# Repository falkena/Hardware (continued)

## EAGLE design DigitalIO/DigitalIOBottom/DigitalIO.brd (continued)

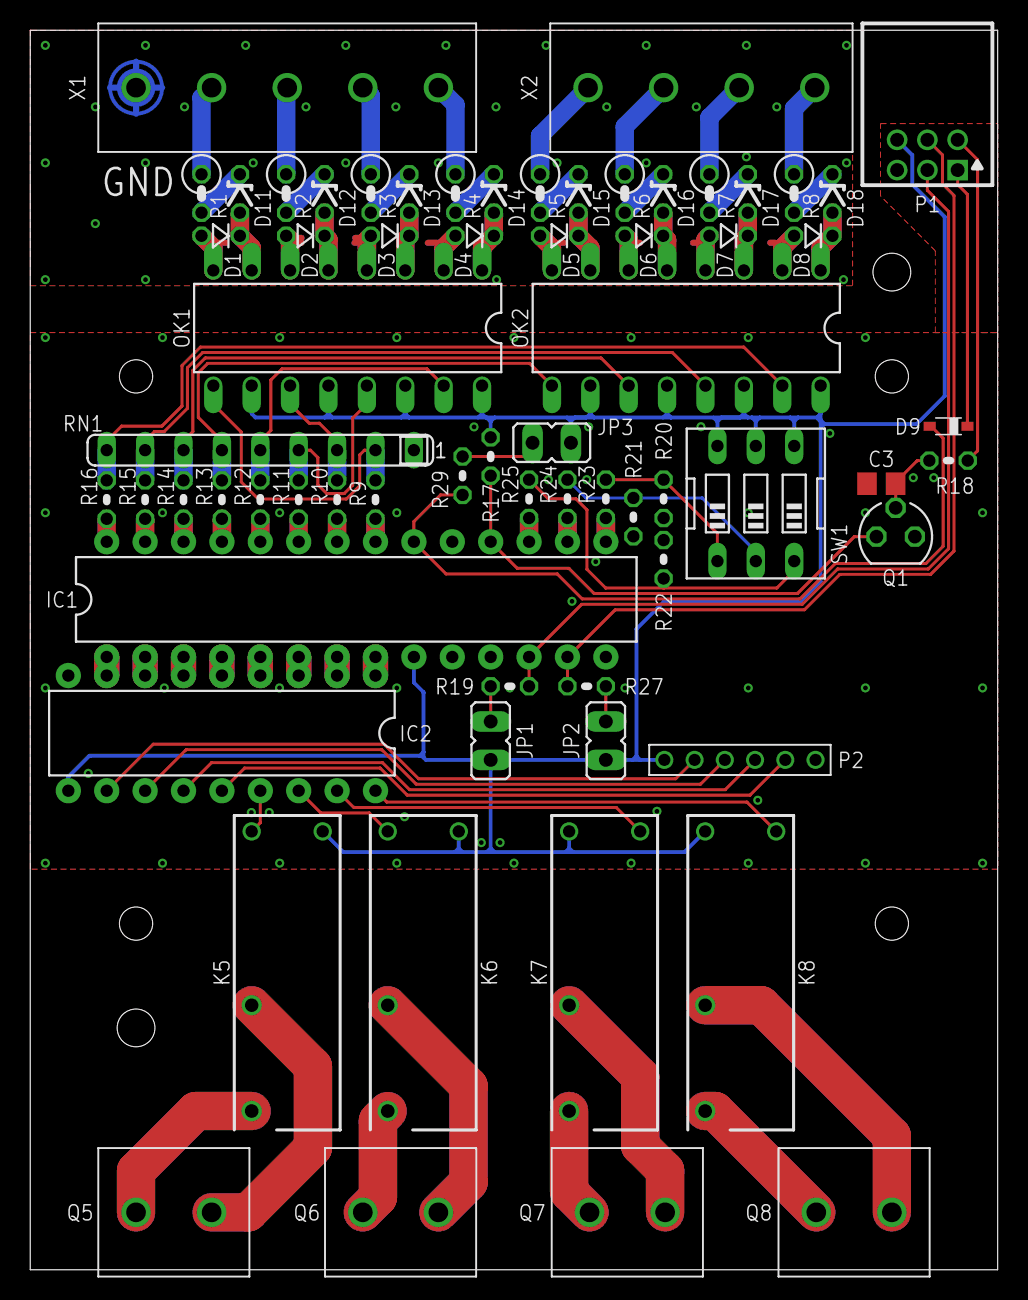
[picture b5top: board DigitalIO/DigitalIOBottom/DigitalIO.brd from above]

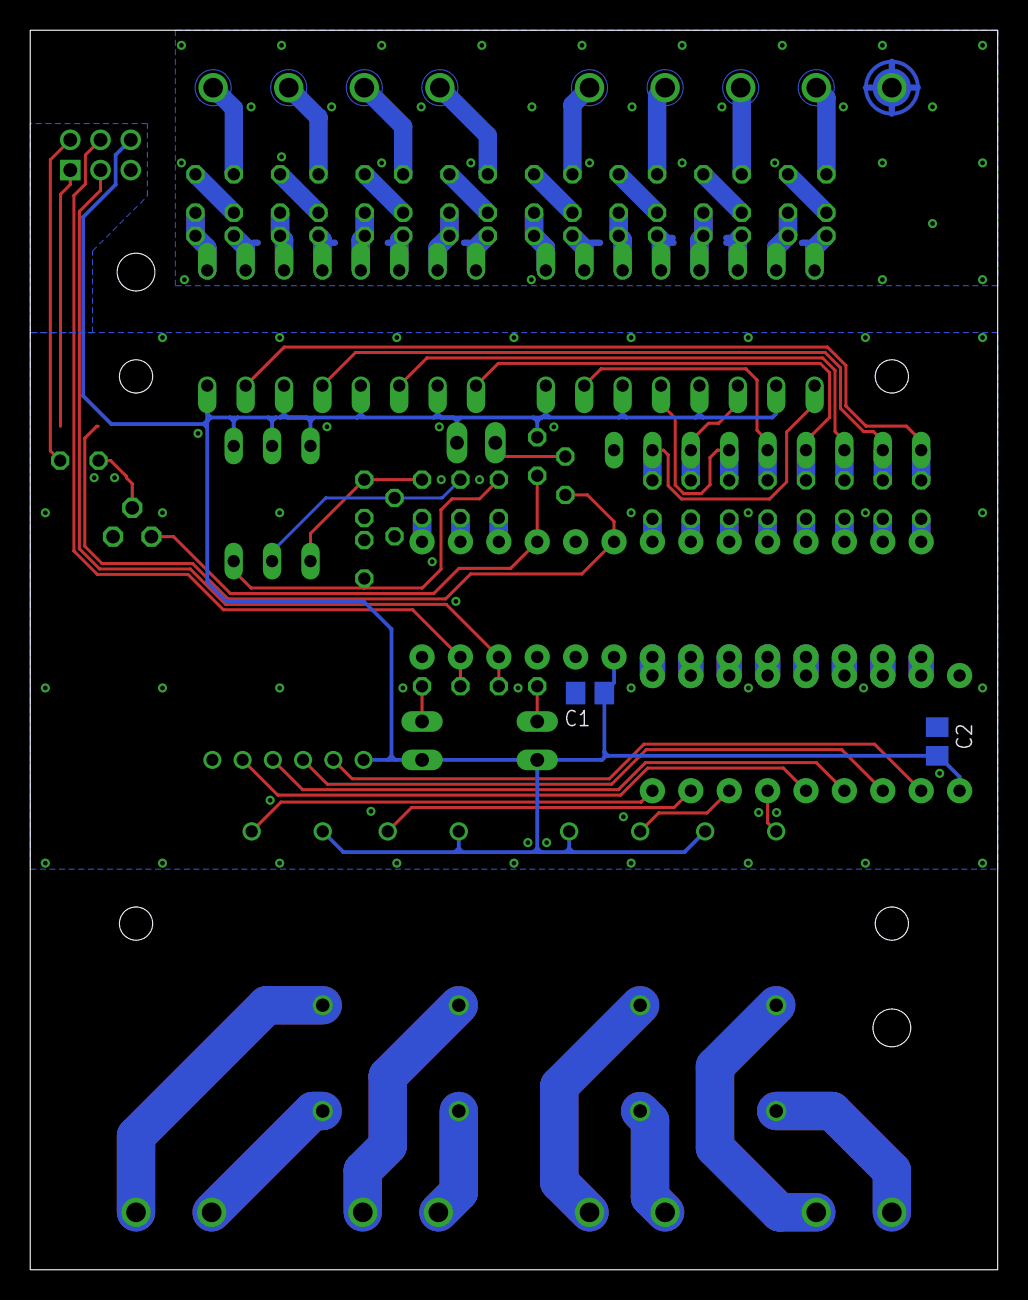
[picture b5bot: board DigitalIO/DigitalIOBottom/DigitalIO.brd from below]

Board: 2 copper layers, 64.0 x 82.0 mm, 69 parts (2 on the bottom side), 83 nets.

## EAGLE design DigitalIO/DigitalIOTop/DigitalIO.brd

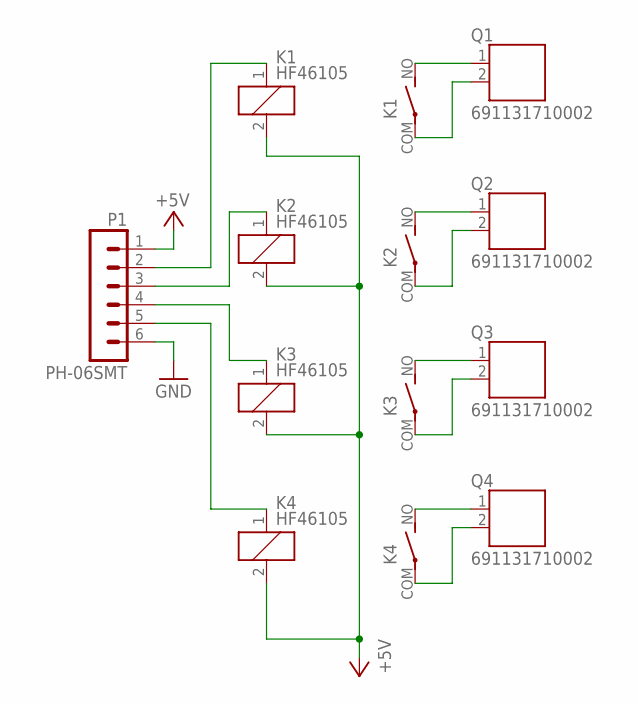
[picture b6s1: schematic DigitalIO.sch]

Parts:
K1, K2, K3, K4: HF46105; HF46
P1: PH-06SMT; S6B-PH-SM4
Q1, Q2, Q3, Q4: 691131710002

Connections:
+5V: K1.2, K2.2, K3.2, K4.2, P1.1
GND: P1.6
unnamed: K2.1, P1.3
unnamed: K4.1, P1.5
unnamed: K1.1, P1.2
unnamed: K1.NO (S), Q1.1
unnamed: K1.COM, Q1.2
unnamed: K2.NO (S), Q2.1
unnamed: K2.COM, Q2.2
unnamed: K3.NO (S), Q3.1
unnamed: K3.COM, Q3.2
unnamed: K4.NO (S), Q4.1
unnamed: K4.COM, Q4.2
unnamed: K3.1, P1.4

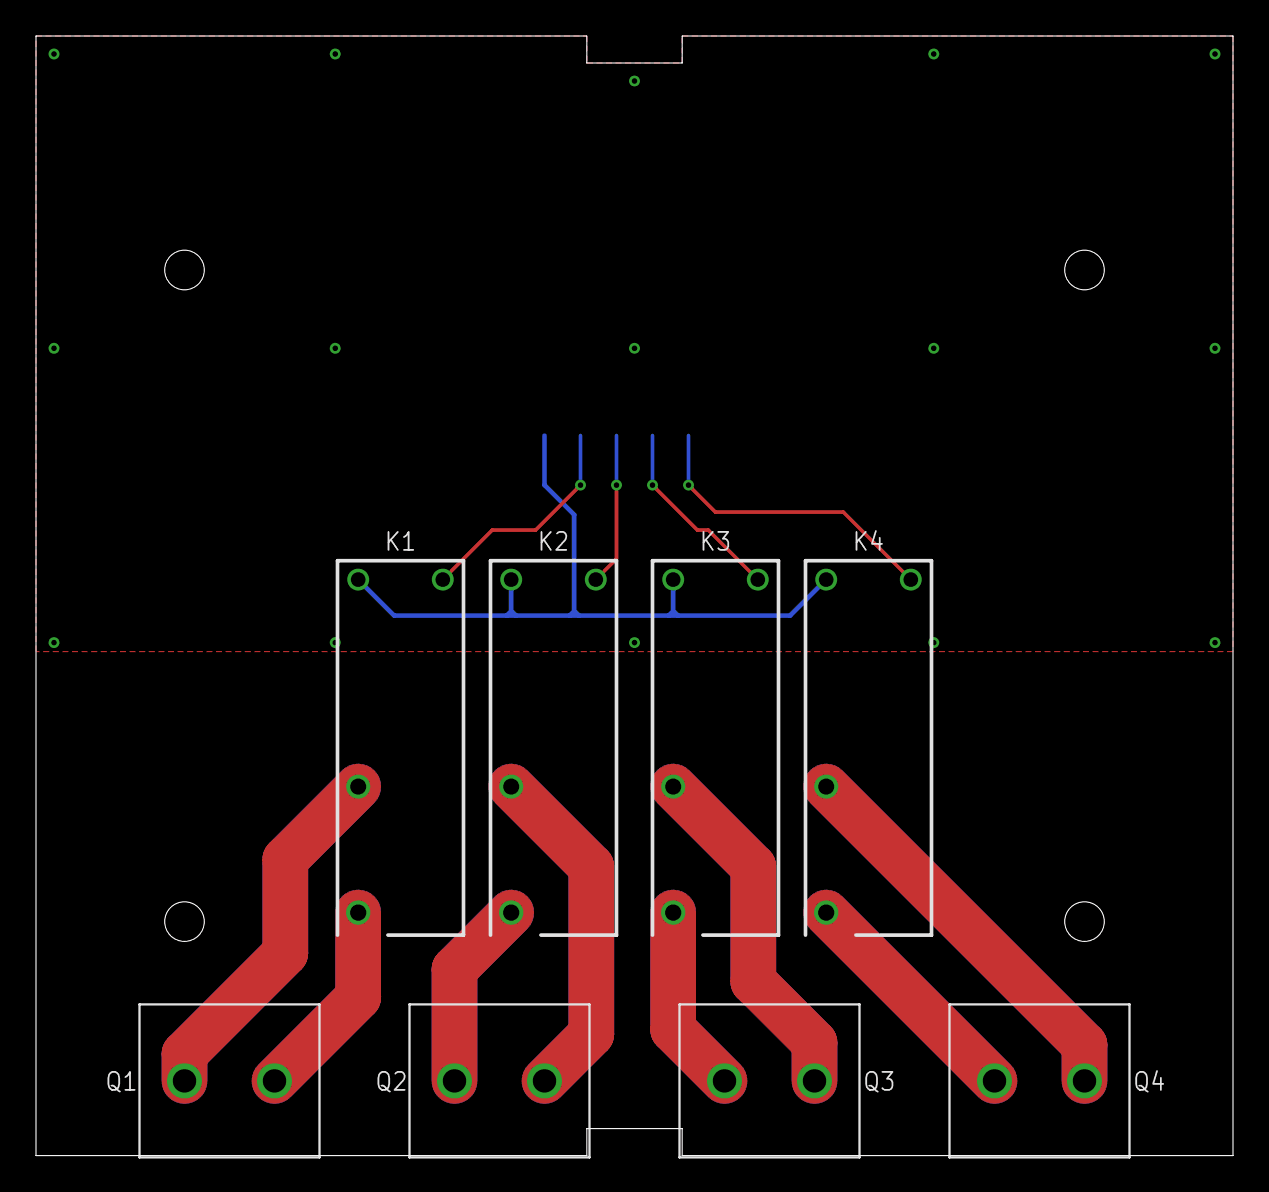
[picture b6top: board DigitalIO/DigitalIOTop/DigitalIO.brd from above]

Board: 2 copper layers, 66.5 x 62.2 mm, 9 parts (1 on the bottom side), 13 nets.

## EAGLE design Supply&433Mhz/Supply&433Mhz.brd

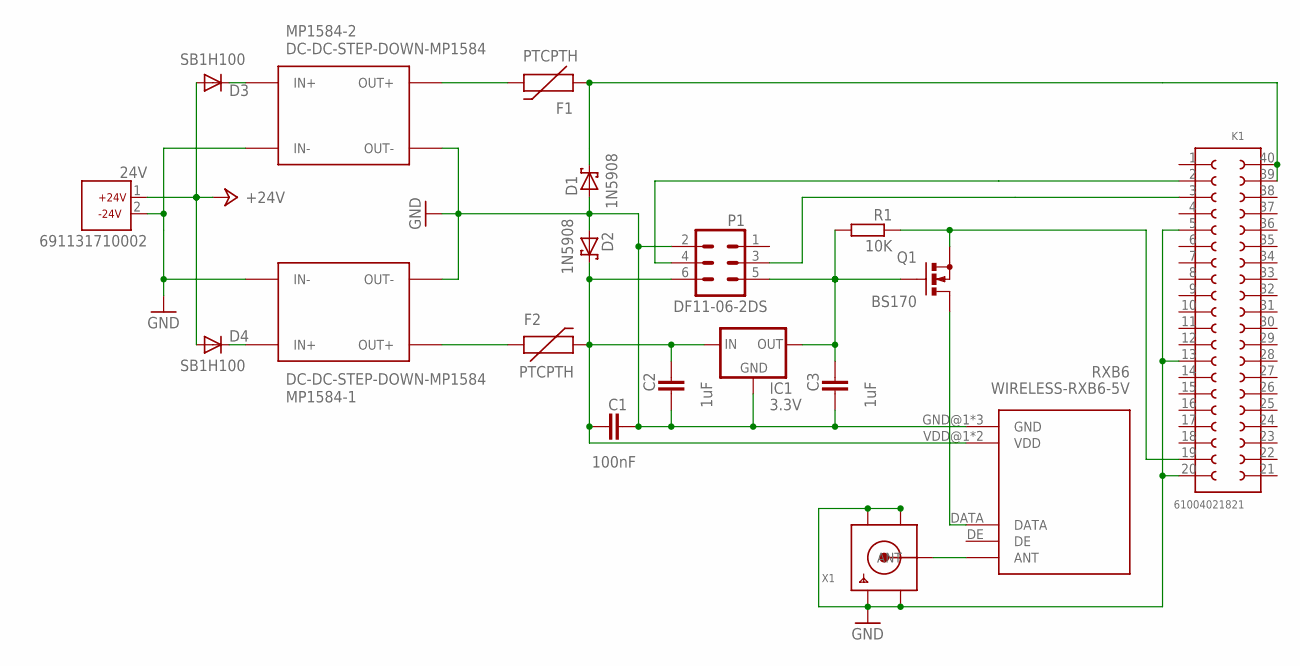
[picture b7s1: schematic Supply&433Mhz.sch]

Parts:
24V: 691131710002
C1: 100nF; C2.5-3
C2, C3: 1uF; C5B3
D1, D2: 1N5908; C4111-15
D3, D4: SB1H100; DO41-7.6
F1, F2: PTCPTH; PTC
IC1: 3.3V; TO92-INLINE
K1: 61004021821
MP1584-1, MP1584-2: DC-DC-STEP-DOWN-MP1584
P1: DF11-06-2DS; DF11-06DP-2DS
Q1: BS170; SOT54E; MPN BS170G
R1: 10K; 0204V
RXB6: WIRELESS-RXB6-5V
X1: SMACONNECTOR; SMA90_DIP

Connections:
+24V: 24V.1, D3.A, D4.A
GND: 24V.2, C1.1, C2.2, C3.2, D1.A, D2.A, IC1.1 (GND), K1.5, K1.13, K1.20, MP1584-1.IN-0 (IN-), MP1584-1.IN-1 (IN-), MP1584-1.OUT-0 (OUT-), MP1584-1.OUT-1 (OUT-), MP1584-2.IN-0 (IN-), MP1584-2.IN-1 (IN-), MP1584-2.OUT-0 (OUT-), MP1584-2.OUT-1 (OUT-), P1.2, RXB6.GND@1 (GND), RXB6.GND@2 (GND), RXB6.GND@3 (GND), X1.GND1, X1.GND2, X1.GND3, X1.GND4
unnamed: K1.3, P1.3
unnamed: C1.2, C2.1, D2.C, F2.P$2 (2), IC1.2 (IN), P1.6, RXB6.VDD@1 (VDD), RXB6.VDD@2 (VDD)
unnamed: Q1.D, RXB6.DATA
unnamed: F1.P$2 (2), MP1584-2.OUT+0 (OUT+), MP1584-2.OUT+1 (OUT+)
unnamed: D1.C, F1.P$1 (1), K1.39, K1.40
unnamed: F2.P$1 (1), MP1584-1.OUT+0 (OUT+), MP1584-1.OUT+1 (OUT+)
unnamed: D3.C, MP1584-2.IN+0 (IN+), MP1584-2.IN+1 (IN+)
unnamed: RXB6.ANT, X1.ANTENNA (ANT)
unnamed: D4.C, MP1584-1.IN+0 (IN+), MP1584-1.IN+1 (IN+)
unnamed: C3.1, IC1.3 (OUT), P1.5, Q1.G, R1.2
unnamed: K1.2, P1.4
unnamed: K1.19, Q1.S, R1.1

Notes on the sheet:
+24V
-24V

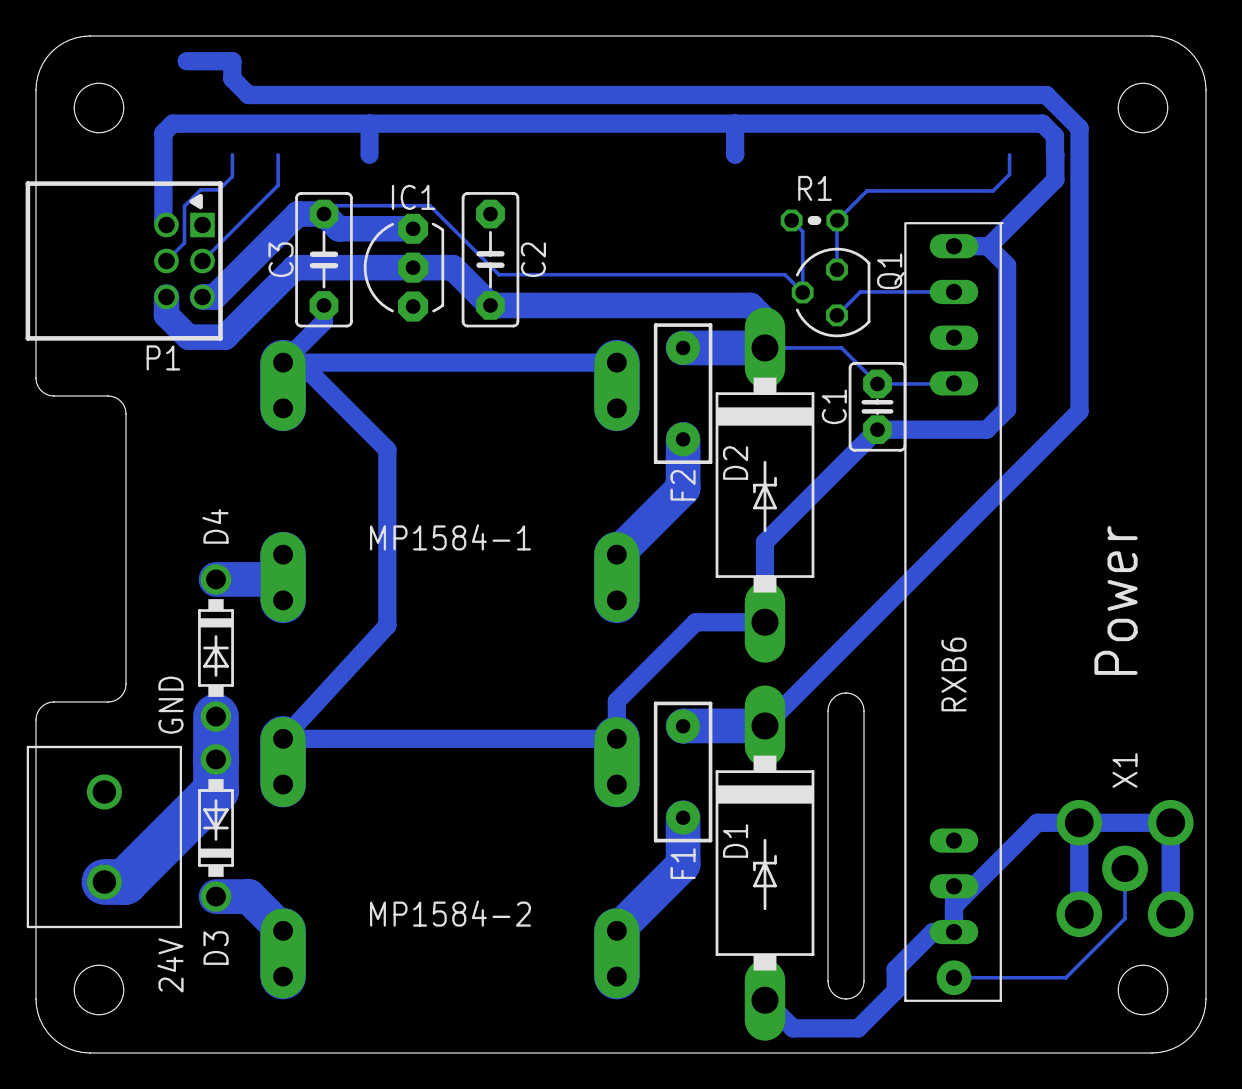
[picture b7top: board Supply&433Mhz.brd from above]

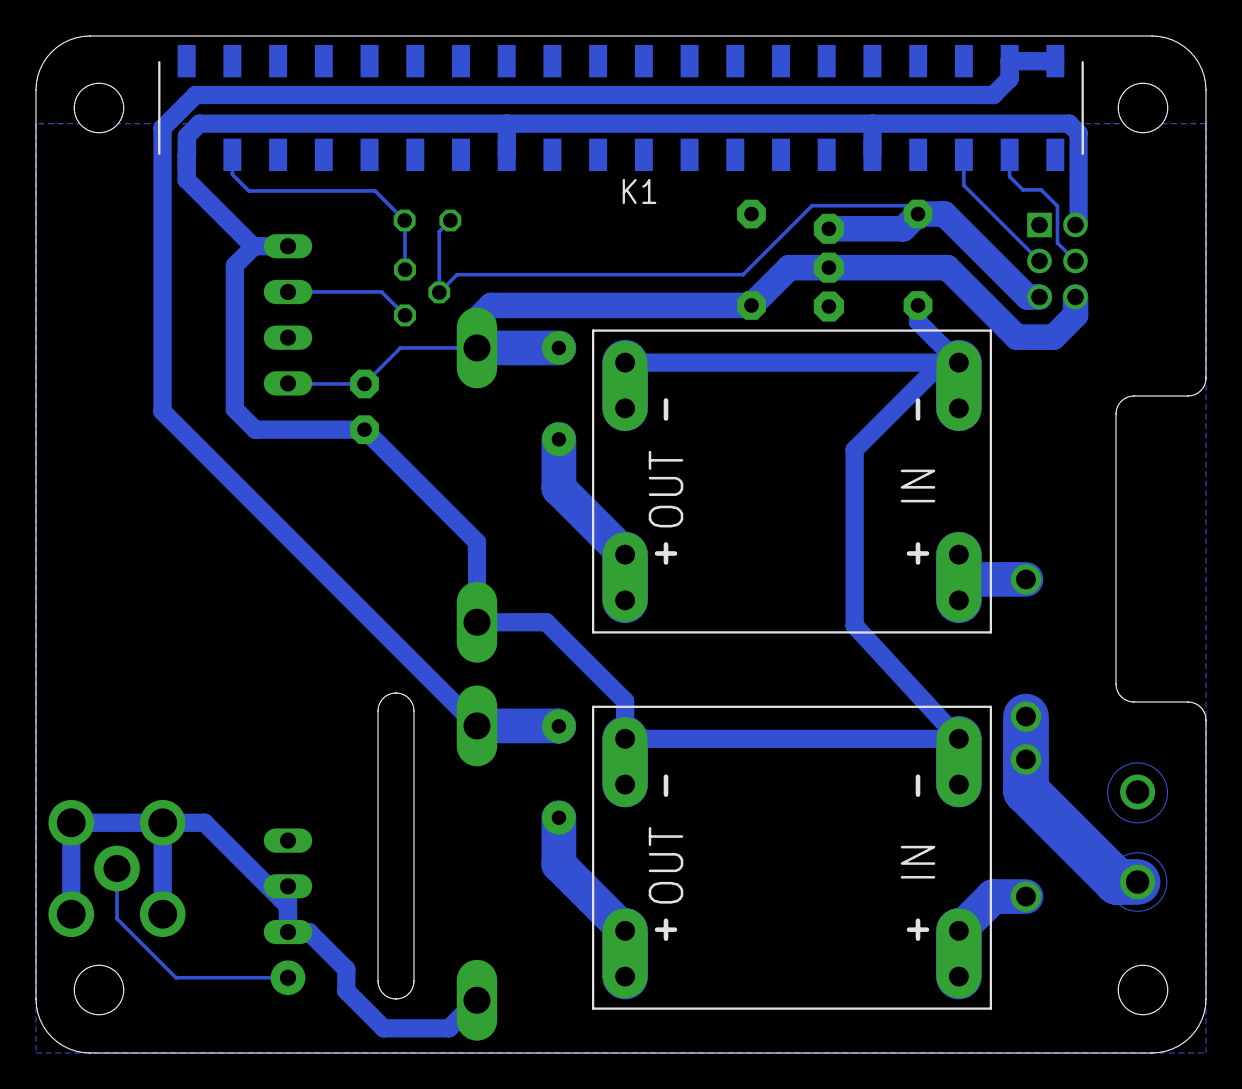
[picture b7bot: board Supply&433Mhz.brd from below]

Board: 2 copper layers, 65.0 x 56.5 mm, 19 parts (3 on the bottom side), 14 nets.

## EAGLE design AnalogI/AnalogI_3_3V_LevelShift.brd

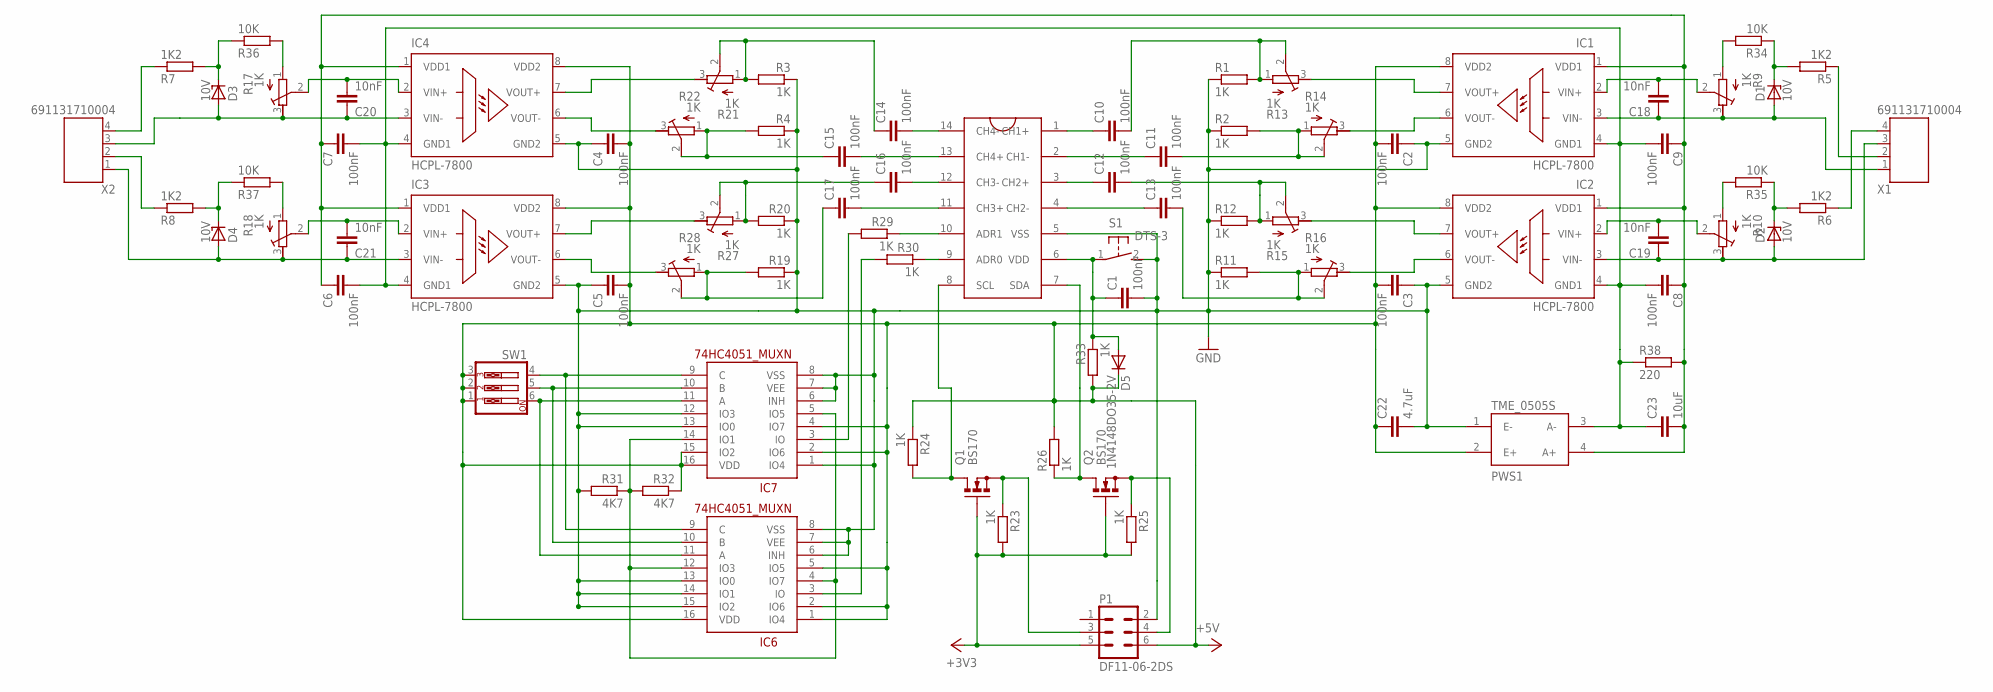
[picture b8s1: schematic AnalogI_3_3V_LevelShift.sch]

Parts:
C1, C2, C3, C4, C5, C6, C7, C8, C9: 100nF; C025-024X044
C10, C11, C12, C13, C14, C15, C16, C17: 100nF; C5B3
C18, C19, C20, C21: 10nF; C2.5-3
C22: 4.7uF; C0805
C23: 10uF; C0805
D1, D2, D3, D4: 10V; ZDIO-2.5
D5: 1N4148DO35-2V; DO35-2V
IC1, IC2, IC3, IC4: HCPL-7800; DIL08
IC5: MCP3424SOIC; 14LDSOIC
IC6, IC7: 74HC4051_MUXN; DIL16
P1: DF11-06-2DS; DF11-06DP-2DS
PWS1: TME_0505S; TMEXXXXS
Q1, Q2: BS170; SOT54E; MPN BS170G
R1, R2, R3, R4, R11, R12, R19, R20, R23, R25, R26, R33: 1K; 0204V
R5, R6, R7, R8: 1K2; 0204V
R9, R10, R13, R14, R15, R16, R17, R18, R21, R22, R27, R28: 1K; RTRIM3296W
R24, R29, R30: 1K; 0204/5
R31, R32: 4K7; 0204V
R34, R35, R36, R37: 10K; 0204V
R38: 220; 0204V
S1: DTS-3
SW1: SW_DIP-3; EDG-03
X1, X2: 691131710004

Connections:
+3V3: P1.5, Q1.G, Q2.G, R23.2, R25.2
+5V: C2.2, C3.2, C4.2, C5.2, C22.1, D5.C, IC1.8 (VDD2), IC2.8 (VDD2), IC3.8 (VDD2), IC4.8 (VDD2), IC6.1 (IO4), IC6.2 (IO6), IC6.5 (IO5), IC6.16 (VDD), IC7.2 (IO6), IC7.4 (IO7), IC7.15 (IO2), IC7.16 (VDD), P1.6, PWS1.2 (E+), R24.1, R26.2, R32.1, R33.2, SW1.1, SW1.2, SW1.3
AGND: C6.2, C7.2, C8.2, C9.2, C23.1, IC1.4 (GND1), IC2.4 (GND1), IC3.4 (GND1), IC4.4 (GND1), PWS1.3 (A-), R38.1
GND: C1.2, C2.1, C3.1, C4.1, C5.1, C22.2, IC1.5 (GND2), IC2.5 (GND2), IC3.5 (GND2), IC4.5 (GND2), IC5.5 (VSS), IC6.6 (INH), IC6.7 (VEE), IC6.8 (VSS), IC6.13 (IO0), IC6.14 (IO1), IC6.15 (IO2), IC7.1 (IO4), IC7.6 (INH), IC7.7 (VEE), IC7.8 (VSS), IC7.12 (IO3), IC7.13 (IO0), P1.2, PWS1.1 (E-), R1.1, R2.1, R3.1, R4.1, R11.1, R12.1, R19.1, R20.1, R31.2, S1.2
unnamed: C14.2, IC5.14 (CH4-)
unnamed: C15.2, IC5.13 (CH4+)
unnamed: C16.2, IC5.12 (CH3-)
unnamed: C17.2, IC5.11 (CH3+)
unnamed: C19.1, D2.A, IC2.3 (VIN-), R10.3 (E), X1.3
unnamed: R5.1, X1.2
unnamed: D1.C, R5.2, R34.1
unnamed: C6.1, C7.1, C8.1, C9.1, C23.2, IC1.1 (VDD1), IC2.1 (VDD1), IC3.1 (VDD1), IC4.1 (VDD1), PWS1.4 (A+), R38.2
unnamed: IC5.10 (ADR1), R29.1
unnamed: IC5.9 (ADR0), R30.1
unnamed: C18.2, IC1.2 (VIN+), R9.2 (S)
unnamed: C19.2, IC2.2 (VIN+), R10.2 (S)
unnamed: C10.1, IC5.1 (CH1+)
unnamed: C20.2, IC4.2 (VIN+), R17.2 (S)
unnamed: C11.1, IC5.2 (CH1-)
unnamed: C21.1, D4.A, IC3.3 (VIN-), R18.3 (E), X2.1
unnamed: C12.1, IC5.3 (CH2+)
unnamed: C12.2, R12.2, R15.1 (A), R15.2 (S)
unnamed: C21.2, IC3.2 (VIN+), R18.2 (S)
unnamed: R6.1, X1.4
unnamed: D2.C, R6.2, R35.1
unnamed: IC1.7 (VOUT+), R13.3 (E)
unnamed: IC1.6 (VOUT-), R14.3 (E)
unnamed: C10.2, R1.2, R13.1 (A), R13.2 (S)
unnamed: IC2.6 (VOUT-), R16.3 (E)
unnamed: IC2.7 (VOUT+), R15.3 (E)
unnamed: C11.2, R2.2, R14.1 (A), R14.2 (S)
unnamed: R7.1, X2.4
unnamed: C13.2, R11.2, R16.1 (A), R16.2 (S)
unnamed: C18.1, D1.A, IC1.3 (VIN-), R9.3 (E), X1.1
unnamed: C13.1, IC5.4 (CH2-)
unnamed: D3.C, R7.2, R36.1
unnamed: R8.1, X2.2
unnamed: D4.C, R8.2, R37.1
unnamed: IC7.3 (IO), R29.2
unnamed: IC6.9 (C), IC7.9 (C), SW1.4
unnamed: IC4.7 (VOUT+), R21.3 (E)
unnamed: IC4.6 (VOUT-), R22.3 (E)
unnamed: C15.1, R4.2, R22.1 (A), R22.2 (S)
unnamed: C20.1, D3.A, IC4.3 (VIN-), R17.3 (E), X2.3
unnamed: C14.1, R3.2, R21.1 (A), R21.2 (S)
unnamed: IC3.6 (VOUT-), R28.3 (E)
unnamed: IC3.7 (VOUT+), R27.3 (E)
unnamed: C17.1, R19.2, R28.1 (A), R28.2 (S)
unnamed: C16.1, R20.2, R27.1 (A), R27.2 (S)
unnamed: IC6.10 (B), IC7.10 (B), SW1.5
unnamed: IC6.11 (A), IC7.11 (A), SW1.6
unnamed: IC6.3 (IO), R30.2
unnamed: IC6.4 (IO7), IC6.12 (IO3), IC7.5 (IO5), IC7.14 (IO1), R31.1, R32.2
unnamed: C1.1, D5.A, IC5.6 (VDD), R33.1, S1.1
unnamed: R9.1 (A), R34.2
unnamed: R10.1 (A), R35.2
unnamed: R17.1 (A), R36.2
unnamed: R18.1 (A), R37.2
unnamed: IC5.8 (SCL), Q1.D, R24.2
unnamed: IC5.7 (SDA), Q2.D, R26.1
unnamed: P1.4, Q2.S, R25.1
unnamed: P1.3, Q1.S, R23.1

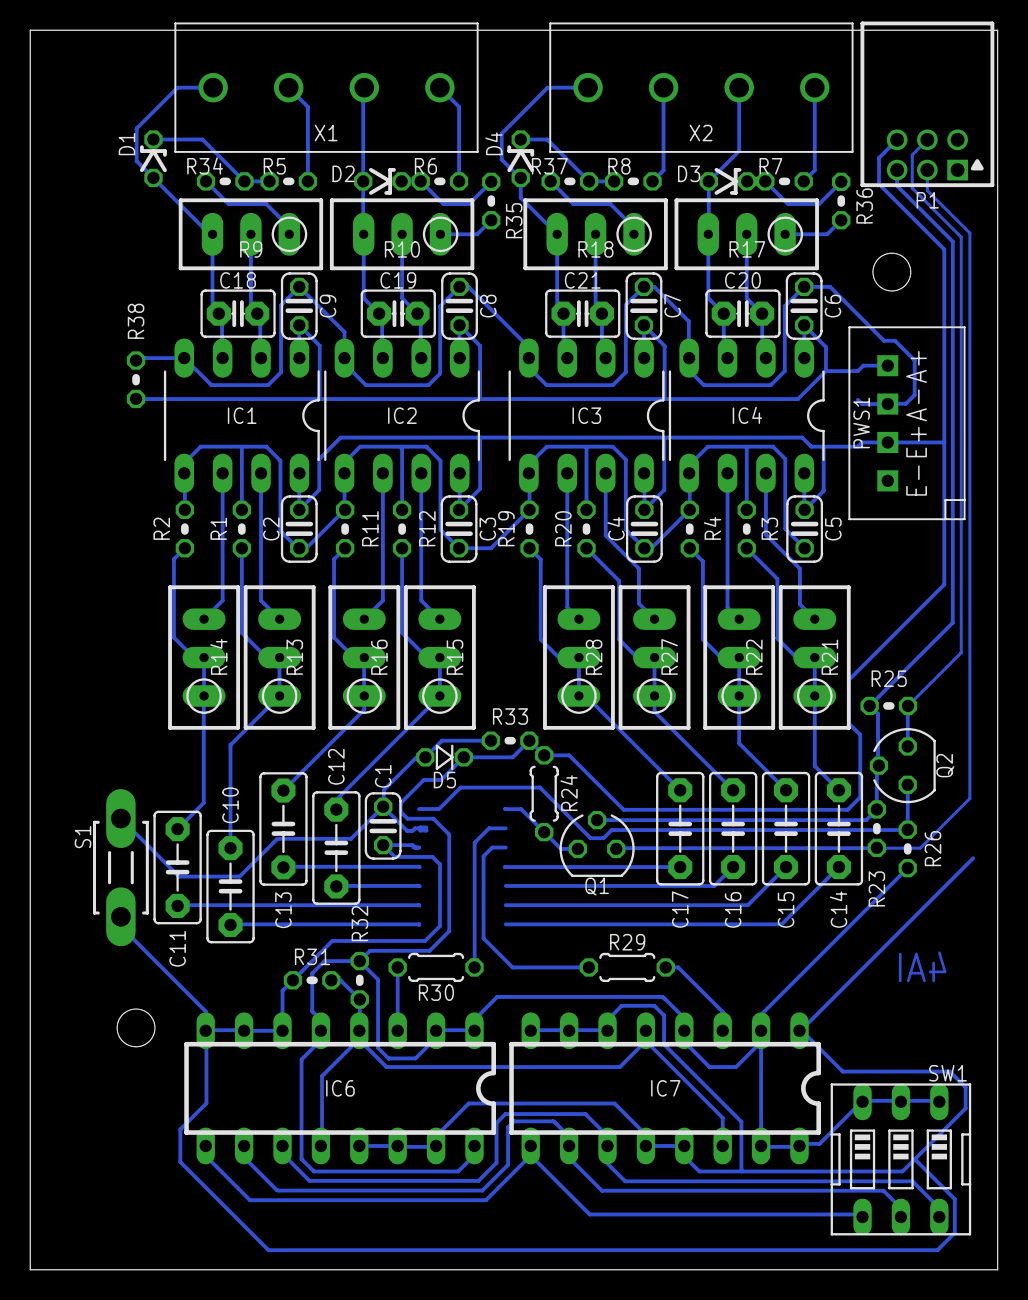
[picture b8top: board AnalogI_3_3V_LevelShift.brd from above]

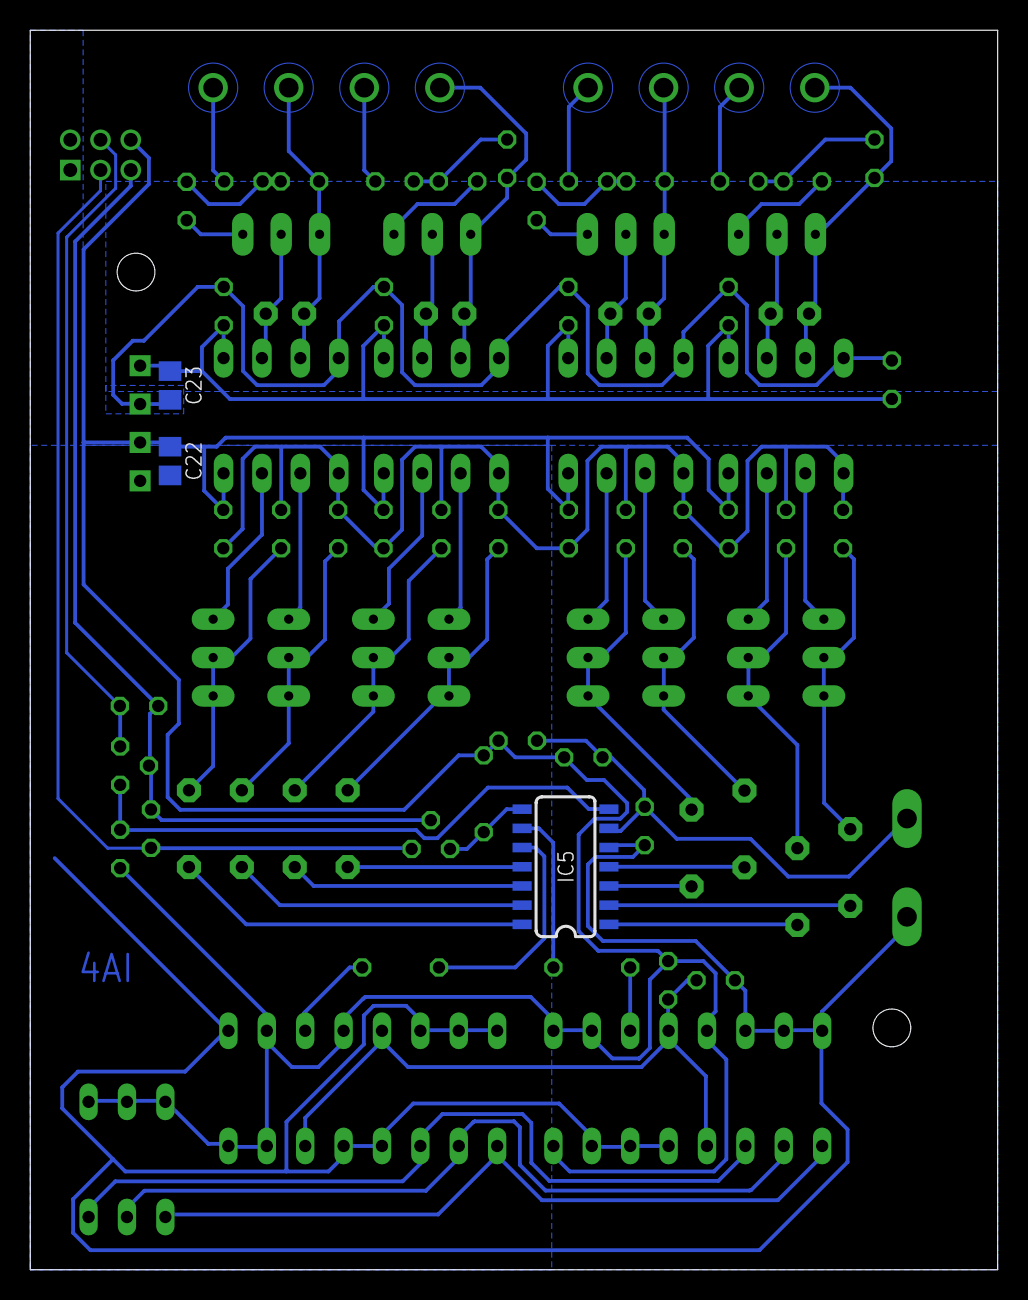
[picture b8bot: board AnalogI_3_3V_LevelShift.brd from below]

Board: 2 copper layers, 64.0 x 82.0 mm, 81 parts (3 on the bottom side), 62 nets.

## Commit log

2016-07-04 Added digital I/O board.
2016-07-05 Added analog I board.
2016-08-26 Initial commit of power supply & rxb6 boards.
2016-08-27 Create component for RXB6 receiver.
2016-08-28 Add capacitors on dc/dc isolator.
2016-08-28 Make ground plate larger.
2016-08-28 Increase drill for dc/dc converter up to 1.1mm.
2016-08-28 Make some drills smaller.
2016-09-02 Change connector positions and drills.
2016-09-03 Change fonts
2016-09-03 Add documentation.
2016-09-03 Increase drill from 2.5mm to 2.75mm. Remove not need holes.
2016-09-03 Remove not need holes.
2016-09-03 Increase font size.
2016-09-03 Changed position of one trace.
2016-09-04 Use vector fonts. Add documentation.
2016-09-04 Change wire width from 6 to 8 mil.
2016-09-05 Increase wire to 8mil.
2016-09-05 Correct position of mounting holes.
2016-09-05 Extend ground plate.
2016-09-05 Change default design rules.
2016-09-05 Add panelized boards for production.
2016-09-05 Documentation added.
2016-09-05 Modified ground plate.
2016-09-26 Changed wire.
2016-09-26 Dimension layer and drills corrected.
2016-09-29 Decrease drills.
2016-09-29 Remove AGND supply, since DC/DC converter use same GND signal.
2016-10-06 Remove Schottky - Diodes, since already on DC/DC buck converter.
2016-10-08 Revert "Remove Schottky - Diodes, since already on DC/DC buck converter."
2016-10-08 Increase drill from 0.5mm to 0.6mm
2016-10-09 Change protection diode from 1N4148 to BS160.
2016-10-09 Increase ground plane.
2016-10-09 Use SB1H100 as protection diode instead of SB160.
2016-10-11 Use 1K as pull-up instead of 10K.
2016-10-14 Replace package for DF11 connector.
2016-10-14 Move PTC and suppressor diodes.
2016-10-15 Increase width of 3.3V trace. Change silkscreen, that DRU run without errors.
2016-10-16 Remove pull-up to 5V since level-shifter worked not properly. Use 10K instead of 1K resistor as pull-up to 3.3V.
2016-10-16 Increase RXB6 drills. Change some wires.
2016-10-17 Use external 3.3V supply instead of raspberry one.
2016-10-19 Remove obsolete files.
2016-10-23 Changed some drills, pads, holes, routes and headers.
2016-10-24 Manufactured board.
2016-10-24 Minor.
2016-10-24 Prepare for production.
2016-10-27 Decrease restriction area.
2016-10-29 Change connector. Modified solder mask.
2016-10-29 Move DC/DC coppler. Update Gerbers.
2016-10-29 Add load resistor.
2016-11-17 Swap 24V supply pins.
2016-12-24 Add power supply, 433Mhz and Homematic support board.
2016-12-26 Move capacitor and pullup resistor.
2016-12-26 Typo corrected.
2016-12-26 Change capacitor position.
2016-12-27 Add simple filter for RXB6 data output.
2016-12-27 Change some wires.
2016-12-28 Remove simple filter for RXB6 data output, since no improvement. Change layout and some wires.
2016-12-29 Make Eagle library for used components.
2016-12-29 Replace RBX6 with RXB8
2016-12-29 Rearrange pins.
2016-12-29 Extend readme. Add license.
2016-12-29 Format was broken.
2016-12-29 Format still broken.
2017-01-03 Decrease drill.
2017-01-20 Fix RXB8 package. Add low pass filter.
2017-01-31 Change low pass capacitor value from 220nF to 100nF.
2017-02-05 Fix low pass filter. Move suppressor diode. Move documentation from top to bottom layer.
2017-02-08 Update design rules. Small changes of ground plane.
2017-02-08 Minor changes of ground plate.
2017-02-09 Add net list. Minor changes to ground plate.
2017-07-01 Add missed terminal legend.
2017-11-15 Add smd package for CC1101 module.
2017-11-15 Replace package for CC1101 receiver
2017-11-15 Change some routes
2017-11-26 Add top ground plate.
2017-11-26 Replace trough hole capacitors with smd
2017-11-27 Add more vias.
2017-12-24 Add raspberry pi library.
2017-12-24 Update to eagle 7.7. Change drill.
2017-12-24 Fix stop mask issues.
2017-12-26 Generate gerber files.
2017-12-30 Fix PTC size.
2018-01-29 Place CC1101 on bottom.
2018-02-04 Add more packages for CC1101 based receiver boards.
2018-02-04 Replace RXB8 with CC1101 receiver.
2018-03-04 Fix export. Remove switch. Prepare board for production.
2018-04-19 Fix footprint. Replace PTC.
2018-04-19 First version of rain sensor board.
2018-04-29 Add fan circuit
2018-06-30 Use SMD PTC's instead of through hole ones.
2019-04-04 Increase drill for mount holes. Add antenna connector legend. Fine tune ground plate contour.
2022-02-19 Remove not need wire.
2022-02-20 Add ground planes. Prepare for production.
2022-03-06 Add raspberry pi 4 device package.
2022-04-23 Fix address selection. Increase some drills.
2022-04-30 Add power switch and I2C interrupt wire. Add pull-up resistors for I2C. Adapt drills.
2022-04-30 Add ground plane on top pcb.
2022-10-19 Rework to operate with 5V only. Add INT and RESET signals.
2022-12-24 Adapt for Raspberry Pi 4. I2C operate with 5V only. Add INT and RESET signals.
2023-01-14 Increase wire width. Add output current limit resistor. Place DC/DC converter vertically.
2024-09-23 Add library for Texas Instrument devices
2024-10-29 Rename Homematic to MainBoard
2024-10-29 Add TRXC2-TIF device. Add footprints for small signal transistors.
2024-11-06 Add Songle SMIH-relay series.
2024-11-06 Rework rain sensor board and make it ready for production.
2024-11-19 Fix rain sensor capacitor footprint
2024-11-30 Replace On/Off fan with PWM driven one
2024-11-30 Extend readme
2024-12-01 Add drop detector
2024-12-09 Add alternative drop detector
2024-12-10 Change project organization
2025-01-03 Fix DC/DC module footprint.
2025-03-14 Add initial layout for Homematic devices based on TRXC2-TIF
